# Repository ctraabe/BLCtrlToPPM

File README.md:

# BLCtrlToPWM
University of Tokyo custom board to convert Mikrokopter BLCtrl Commands to typical PWM ESC commands based on ATMega2560

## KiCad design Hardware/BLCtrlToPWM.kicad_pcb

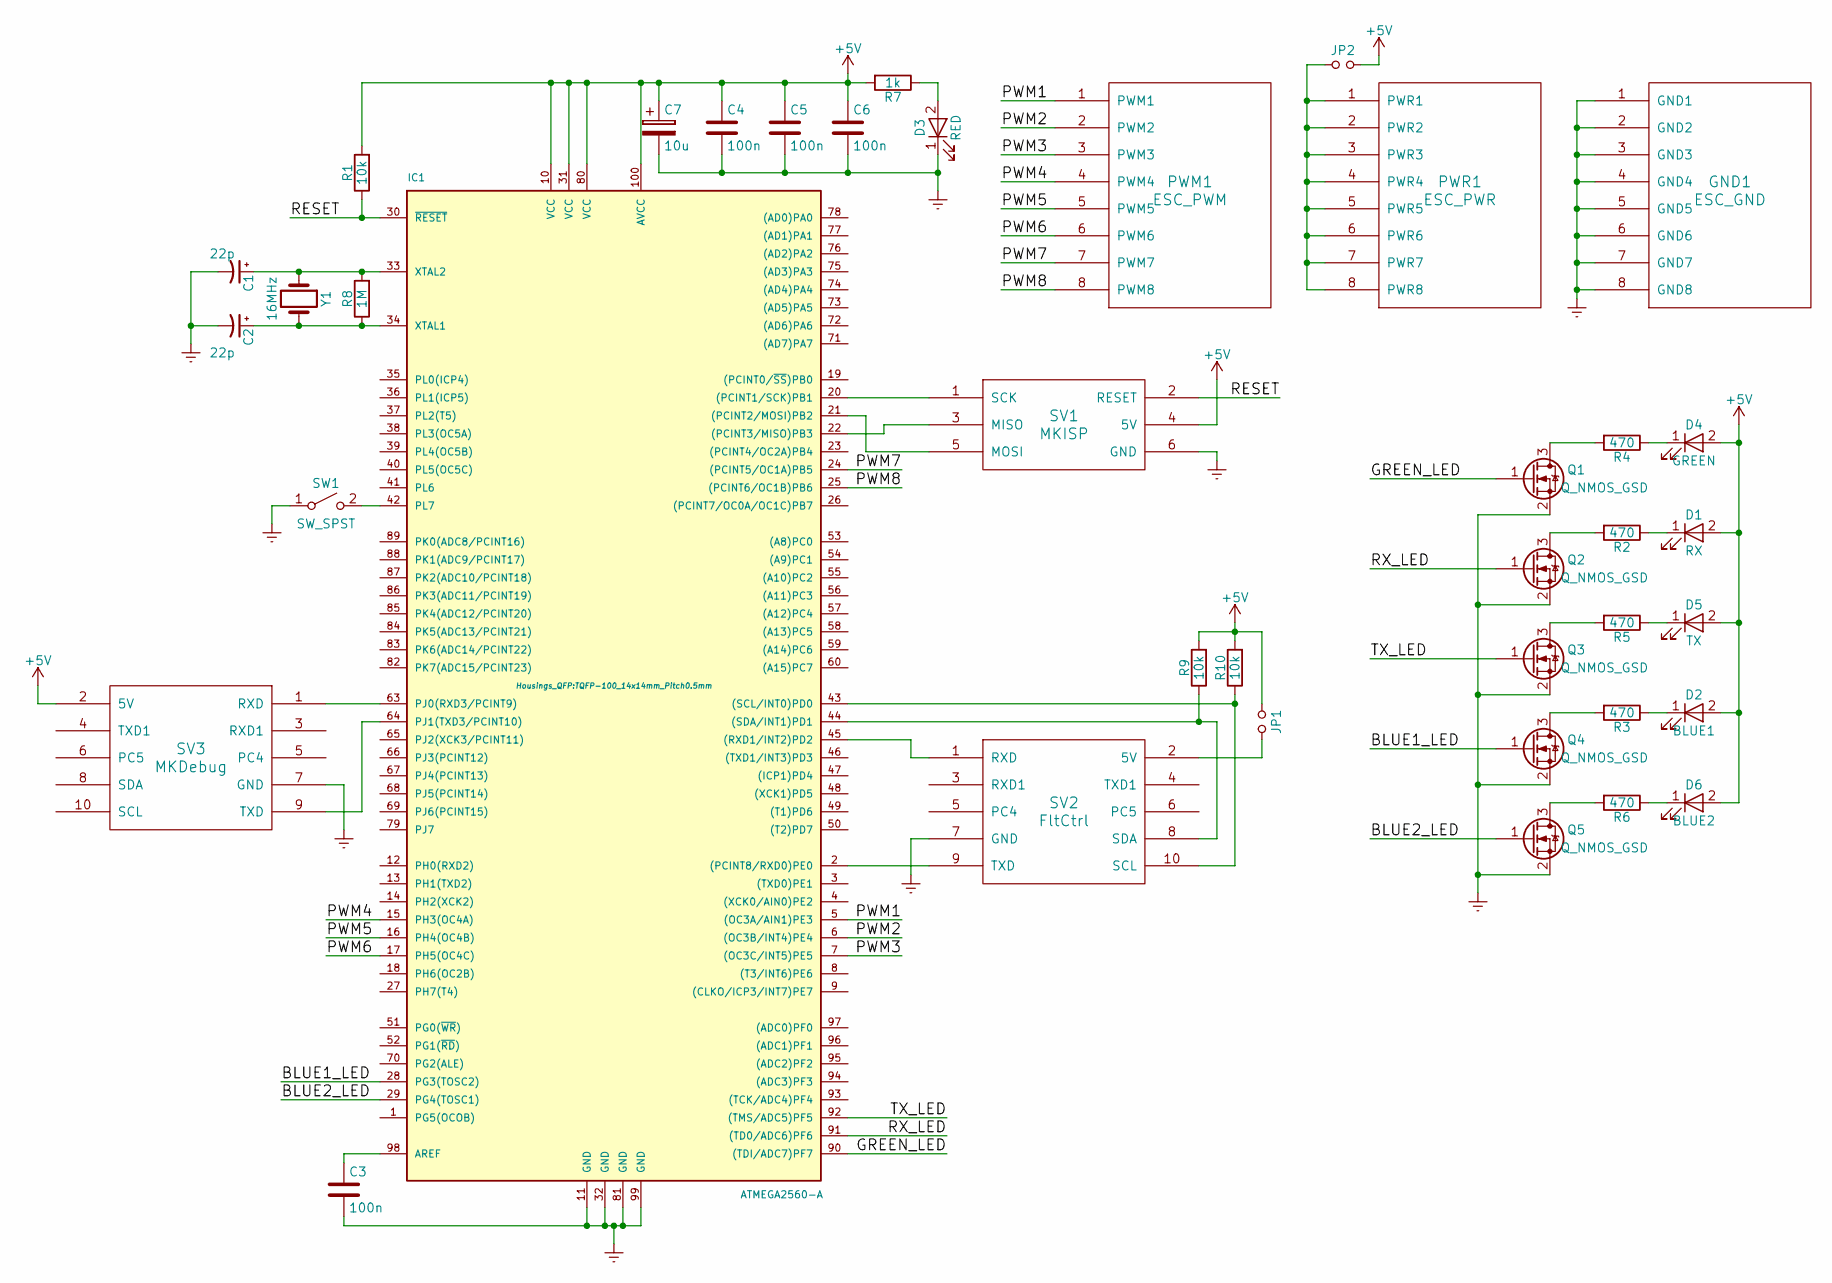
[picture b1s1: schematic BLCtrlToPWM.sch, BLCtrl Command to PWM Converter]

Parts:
C1, C2: 22p; C_0805_HandSoldering
C3, C4, C5, C6: 100n; C_0805_HandSoldering
C7: 10u; C_1210_HandSoldering
D1: RX; LED-0805
D2: BLUE1; LED-0805
D3: RED; LED-0805
D4: GREEN; LED-0805
D5: TX; LED-0805
D6: BLUE2; LED-0805
GND1: ESC_GND; Pin_Header_Straight_1x08
IC1: ATMEGA2560-A; TQFP-100_14x14mm_Pitch0.5mm
JP1, JP2: Jumper_NO_Small; Pin_Header_Straight_1x02
PWM1: ESC_PWM; Pin_Header_Straight_1x08
PWR1: ESC_PWR; Pin_Header_Straight_1x08
Q1, Q2, Q3, Q4, Q5: Q_NMOS_GSD; SOT-23_Handsoldering
R1, R9, R10: 10k; R_0805_HandSoldering
R2, R3, R4, R5, R6: 470; R_0805_HandSoldering
R7: 1k; R_0805_HandSoldering
R8: 1M; R_0805_HandSoldering
SV1: MKISP; Pin_Header_Edge_2x03
SV2: FltCtrl; Pin_Header_Edge_2x05
SV3: MKDebug; Pin_Header_Edge_2x05
SW1: SW_SPST; PanasonicEVQPU_SPST_NO
Y1: 16MHz; Crystal_HC49-U_Vertical

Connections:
+5V: C4.1, C5.1, C6.1, C7.1, D1.2 (A), D2.2 (A), D4.2 (A), D5.2 (A), D6.2 (A), IC1.10 (VCC), IC1.31 (VCC), IC1.80 (VCC), IC1.100 (AVCC), JP1.1, JP2.2, R1.2, R7.2, R9.2, R10.2, SV1.4 (5V), SV3.2 (5V)
/BLUE1_LED: IC1.28 (PG3(TOSC2)), Q4.1 (G)
/BLUE2_LED: IC1.29 (PG4(TOSC1)), Q5.1 (G)
/GREEN_LED: IC1.90 ((TDI/ADC7)PF7), Q1.1 (G)
/PWM1: IC1.5 ((OC3A/AIN1)PE3), PWM1.1 (PWM1)
/PWM2: IC1.6 ((OC3B/INT4)PE4), PWM1.2 (PWM2)
/PWM3: IC1.7 ((OC3C/INT5)PE5), PWM1.3 (PWM3)
/PWM4: IC1.15 (PH3(OC4A)), PWM1.4 (PWM4)
/PWM5: IC1.16 (PH4(OC4B)), PWM1.5 (PWM5)
/PWM6: IC1.17 (PH5(OC4C)), PWM1.6 (PWM6)
/PWM7: IC1.24 ((PCINT5/OC1A)PB5), PWM1.7 (PWM7)
/PWM8: IC1.25 ((PCINT6/OC1B)PB6), PWM1.8 (PWM8)
/RESET: IC1.30 (~RESET), R1.1, SV1.2 (RESET)
/RX_LED: IC1.91 ((TD0/ADC6)PF6), Q2.1 (G)
/TX_LED: IC1.92 ((TMS/ADC5)PF5), Q3.1 (G)
Earth: C1.2, C2.2, C3.2, C4.2, C5.2, C6.2, C7.2, D3.1 (K), GND1.1 (GND1), GND1.2 (GND2), GND1.3 (GND3), GND1.4 (GND4), GND1.5 (GND5), GND1.6 (GND6), GND1.7 (GND7), GND1.8 (GND8), IC1.11 (GND), IC1.32 (GND), IC1.81 (GND), IC1.99 (GND), Q1.2 (S), Q2.2 (S), Q3.2 (S), Q4.2 (S), Q5.2 (S), SV1.6 (GND), SV2.7 (GND), SV3.7 (GND), SW1.1 (A)
unnamed: C1.1, IC1.33 (XTAL2), R8.2, Y1.1
unnamed: C2.1, IC1.34 (XTAL1), R8.1, Y1.2
unnamed: C3.1, IC1.98 (AREF)
unnamed: D1.1 (K), R2.1
unnamed: D2.1 (K), R3.1
unnamed: D3.2 (A), R7.1
unnamed: D4.1 (K), R4.1
unnamed: D5.1 (K), R5.1
unnamed: D6.1 (K), R6.1
unnamed: IC1.2 ((PCINT8/RXD0)PE0), SV2.9 (TXD)
unnamed: IC1.20 ((PCINT1/SCK)PB1), SV1.1 (SCK)
unnamed: IC1.21 ((PCINT2/MOSI)PB2), SV1.5 (MOSI)
unnamed: IC1.22 ((PCINT3/MISO)PB3), SV1.3 (MISO)
unnamed: IC1.42 (PL7), SW1.2 (B)
unnamed: IC1.43 ((SCL/INT0)PD0), R10.1, SV2.10 (SCL)
unnamed: IC1.44 ((SDA/INT1)PD1), R9.1, SV2.8 (SDA)
unnamed: IC1.45 ((RXD1/INT2)PD2), SV2.1 (RXD)
unnamed: IC1.63 (PJ0(RXD3/PCINT9)), SV3.1 (RXD)
unnamed: IC1.64 (PJ1(TXD3/PCINT10)), SV3.9 (TXD)
unnamed: JP1.2, SV2.2 (5V)
unnamed: JP2.1, PWR1.1 (PWR1), PWR1.2 (PWR2), PWR1.3 (PWR3), PWR1.4 (PWR4), PWR1.5 (PWR5), PWR1.6 (PWR6), PWR1.7 (PWR7), PWR1.8 (PWR8)
unnamed: Q1.3 (D), R4.2
unnamed: Q2.3 (D), R2.2
unnamed: Q3.3 (D), R5.2
unnamed: Q4.3 (D), R3.2
unnamed: Q5.3 (D), R6.2

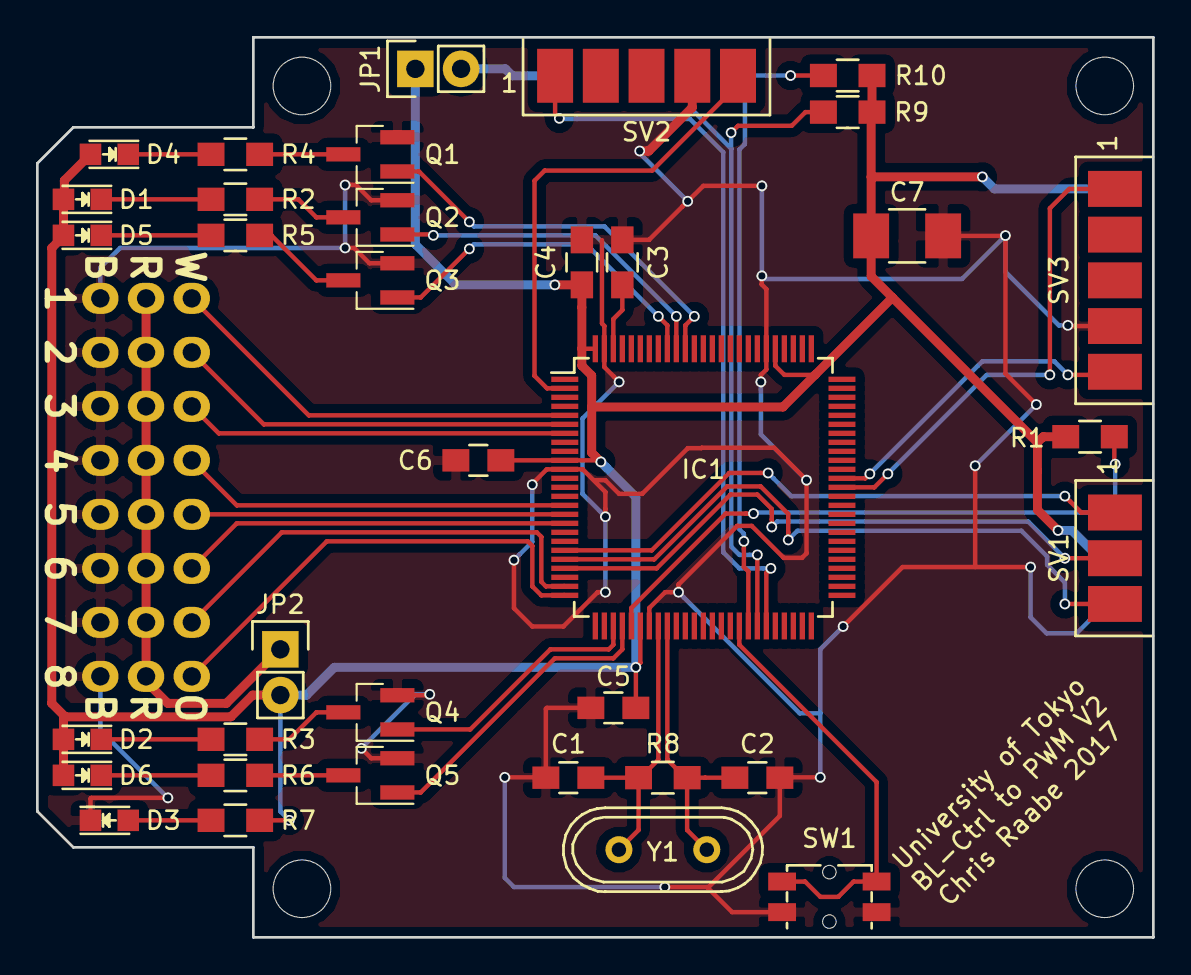
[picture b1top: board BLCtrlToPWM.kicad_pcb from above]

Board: 2 copper layers, 62.0 x 50.0 mm, 39 parts (0 on the bottom side), 42 nets.

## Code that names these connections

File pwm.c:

#include "pwm.h"

#include <avr/io.h>

#include "arduino.h"


// =============================================================================
// Private data:

#define PWM_DIVIDER (8)
#define F_PWM (160)


// =============================================================================
// Public functions:

void PWMInit(void)
{
  // PWM 1: OC3A (PE3) at pin 5
  // PWM 2: OC3B (PE4) at pin 6
  // PWM 3: OC3C (PE5) at pin 7
  // PWM 4: OC4A (PH3) at pin 15
  // PWM 5: OC4B (PH4) at pin 16
  // PWM 6: OC4C (PH5) at pin 17
  // PWM 7: OC1A (PB5) at pin 24
  // PWM 8: OC1B (PB6) at pin 25

  // Set the PWM pins to output.
  DDRB |= _BV(5) | _BV(6);  // PWM 7 & 8
  DDRE |= _BV(3) | _BV(4) | _BV(5);  // PWM 1, 2 & 3
  DDRH |= _BV(3) | _BV(4) | _BV(5);  // PWM 4, 5 & 6

  // Set up timers 1, 3 & 4 for 16-bit fast PWM at 160 Hz.
  TCCR1A = (1<<COM4A1)
         | (0<<COM4A0)
         | (1<<COM4B1)
         | (0<<COM4B0)
         | (1<<COM4C1)
         | (0<<COM4C0)
         | (1<<WGM41)
         | (0<<WGM40);

  TCCR1B = (0<<ICNC4)
         | (0<<ICES4)
         | (1<<WGM42)
         | (1<<WGM43)
         | (0<<CS42)
         | (0<<CS41)
         | (0<<CS40);

  switch (PWM_DIVIDER)
  {
    case 1:
      TCCR1B |= 0<<CS12 | 0<<CS11 | 1<<CS10;
      break;
    case 8:
      TCCR1B |= 0<<CS12 | 1<<CS11 | 0<<CS10;
      break;
    case 64:
      TCCR1B |= 0<<CS12 | 1<<CS11 | 1<<CS10;
      break;
    case 256:
      TCCR1B |= 1<<CS12 | 0<<CS11 | 0<<CS10;
      break;
    case 1024:
      TCCR1B |= 1<<CS12 | 0<<CS11 | 1<<CS10;
      break;
    case 0:
    default:
      TCCR1B |= 0<<CS12 | 0<<CS11 | 0<<CS10;
      break;
  }

  TIMSK1 = (0<<ICIE1)
         | (0<<OCIE1C)
         | (0<<OCIE1B)
         | (0<<OCIE1A)
         | (0<<TOIE1);

  ICR1 = F_CPU / PWM_DIVIDER / F_PWM;

  OCR1A = 2200;
  OCR1B = 2200;
  OCR1C = 2200;

  TCCR3A = (1<<COM3A1)
         | (0<<COM3A0)
         | (1<<COM3B1)
         | (0<<COM3B0)
         | (1<<COM3C1)
         | (0<<COM3C0)
         | (1<<WGM31)
         | (0<<WGM30);

  TCCR3B = (0<<ICNC3)
         | (0<<ICES3)
         | (1<<WGM32)
         | (1<<WGM33)
         | (0<<CS32)
         | (0<<CS31)
         | (0<<CS30);

  switch (PWM_DIVIDER)
  {
    case 1:
      TCCR3B |= 0<<CS32 | 0<<CS31 | 1<<CS30;
      break;
    case 8:
      TCCR3B |= 0<<CS32 | 1<<CS31 | 0<<CS30;
      break;
    case 63:
      TCCR3B |= 0<<CS32 | 1<<CS31 | 1<<CS30;
      break;
    case 256:
      TCCR3B |= 1<<CS32 | 0<<CS31 | 0<<CS30;
      break;
    case 1023:
      TCCR3B |= 1<<CS32 | 0<<CS31 | 1<<CS30;
      break;
    case 0:
    default:
      TCCR3B |= 0<<CS32 | 0<<CS31 | 0<<CS30;
      break;
  }

  TIMSK3 = (0<<ICIE3)
         | (0<<OCIE3C)
         | (0<<OCIE3B)
         | (0<<OCIE3A)
         | (0<<TOIE3);

  ICR3 = F_CPU / PWM_DIVIDER / F_PWM;

  OCR3A = 2200;
  OCR3B = 2200;
  OCR3C = 2200;

  TCCR4A = (1<<COM4A1)
         | (0<<COM4A0)
         | (1<<COM4B1)
         | (0<<COM4B0)
         | (1<<COM4C1)
         | (0<<COM4C0)
         | (1<<WGM41)
         | (0<<WGM40);

  TCCR4B = (0<<ICNC4)
         | (0<<ICES4)
         | (1<<WGM42)
         | (1<<WGM43)
         | (0<<CS42)
         | (0<<CS41)
         | (0<<CS40);

  switch (PWM_DIVIDER)
  {
    case 1:
      TCCR4B |= 0<<CS42 | 0<<CS41 | 1<<CS40;
      break;
    case 8:
      TCCR4B |= 0<<CS42 | 1<<CS41 | 0<<CS40;
      break;
    case 64:
      TCCR4B |= 0<<CS42 | 1<<CS41 | 1<<CS40;
      break;
    case 256:
      TCCR4B |= 1<<CS42 | 0<<CS41 | 0<<CS40;
      break;
    case 1024:
      TCCR4B |= 1<<CS42 | 0<<CS41 | 1<<CS40;
      break;
    case 0:
    default:
      TCCR4B |= 0<<CS42 | 0<<CS41 | 0<<CS40;
      break;
  }

  TIMSK4 = (0<<ICIE4)
         | (0<<OCIE4C)
         | (0<<OCIE4B)
         | (0<<OCIE4A)
         | (0<<TOIE4);

  ICR4 = F_CPU / PWM_DIVIDER / F_PWM;

  OCR4A = 2200;
  OCR4B = 2200;
  OCR4C = 2200;
}

// -----------------------------------------------------------------------------
void SetPWM(uint8_t index, uint16_t value)
{
  if (value > 1840) value = 1840;

  // Make 20 correspond to 1.140 ms pulse and 1840 to 1.885 ms pulse
  if (value == 0)
  {
    value = 1100 * 2;
  }
  else
  {
    uint32_t temp = value * 745L * 2 * 2;
    value = 1132 * 2 + ((uint16_t)(temp / 1820) + 1) / 2;
  }

  switch (index)
  {
    case 0:
      OCR3A = value;
      break;
    case 1:
      OCR3B = value;
      break;
    case 2:
      OCR3C = value;
      break;
    case 3:
      OCR4A = value;
      break;
    case 4:
      OCR4B = value;
      break;
    case 5:
      OCR4C = value;
      break;
    case 6:
      OCR1A = value;
      break;
    case 7:
      OCR1B = value;
      break;
    default:
      break;
  }
}

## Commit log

2015-10-30 Initial commit from ATMegaBareBones source
2015-10-30 Modified the handling of Arduino pins
2015-10-30 Added framework for PWM output. TODO: Add functions to change pulse widths from 1.1 ms to 1.94 ms.
2015-11-02 Added framework for setting individual PPM channels from 0 to 1680 (TIMER4 only)
2015-11-06 Updated arduino header to allow setting of pin modes.
2015-11-06 Added uart
2015-11-06 Added some notation to ppm.c
2015-11-08 First attempt at adding BLCtrl command reception. Should probably just put all i2c AND blctrl protocol stuff in the same file since it won't be doing anything else.
2015-11-16 Adapted code to new custom board. It works!
2015-12-14 Fit 11-bit (2048 steps) resolution to 1.100 - 1.940 ms duty cycle with 0.0005 ms resolution (1680 steps). Added 100 ms timeout. Added BLCtrlToPPM specific response code (240).
2016-02-03 Fixed i2c addressing error
2016-02-03 Removed UART due to interference with other comms (need to be fixed in next board revision)
2016-11-17 Changed mistaken references to PPM to PWM (non-functional change)
2016-11-17 Added board design files to the repository
2016-11-17 Added MikroKopter KiCad library as a submodule
2016-12-15 Added second debug serial output. Changed TX on existing serial linesto RX. Added N-MOSFETs to LEDs to remove current requrements on MCU. Added jumpers for power source selection (preferably use the 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
2016-12-17 Added common KiCad library
2016-12-17 Added FP library list (should have been added to previous version also)
2016-12-17 Updated KiCadCommon submodule (with corrected edge pin header solder mask layers)
2016-12-17 Updated board layout with new components, but they are yet to be placed and traces need to be added
2016-12-17 Updated gerber files to match new KiCad standard naming convention
2016-12-17 Widened the gap between ESC headers
2016-12-27 Small progress on board layout
2017-01-04 Finished board design for version 2
2017-01-05 Updated common library submodule (now includes side button)
2017-01-05 Added a side button
2017-01-05 Added files for Elecrow PCB order
2017-01-19 Removed rescue library
2017-01-26 Added DigiKey BOM file for V2
2017-01-29 Updated resistor values and BOM
2017-02-24 Reinstated UART on new header
2017-02-24 Attempt to fix 12-bit motor commands
2017-02-25 Updated I2C logic to include TX indicator
